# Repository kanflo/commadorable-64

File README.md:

# Commadorable 64

An adorable Commodore 64 desktop ornament. Blog post [here](http://johan.kanflo.com/the-commadorable-64/).

**Howto**

Assuming you have cloned the EOR git and set your wifi credentials:

```
export EOR_ROOT=/path/to/esp-open-rtos
cd $EOR_ROOT
git clone https://github.com/kanflo/eor-arduino-compat.git extras/arduino-compat
git clone https://github.com/kanflo/eor-adafruit-ili9341.git extras/ili9341
git clone https://github.com/kanflo/eor-cli.git extras/cli
cd /path/to/wherever
git clone https://github.com/kanflo/commadorable-64.git
cd commadorable-64
make -j8 && make flash
```

**Ordering the PCB**

The PCBs can be ordered from DirtyPCBs.com, [without touch](http://dirtypcbs.com/view.php?share=18116&accesskey=5cb9ea9c4754e5c9102b4350393b244e) or [with touch](http://dirtypcbs.com/view.php?share=18114&accesskey=f7144fbd88f9270b40ccc2829f08ee2f). If you use these links to order I will receive a $1 credit :)

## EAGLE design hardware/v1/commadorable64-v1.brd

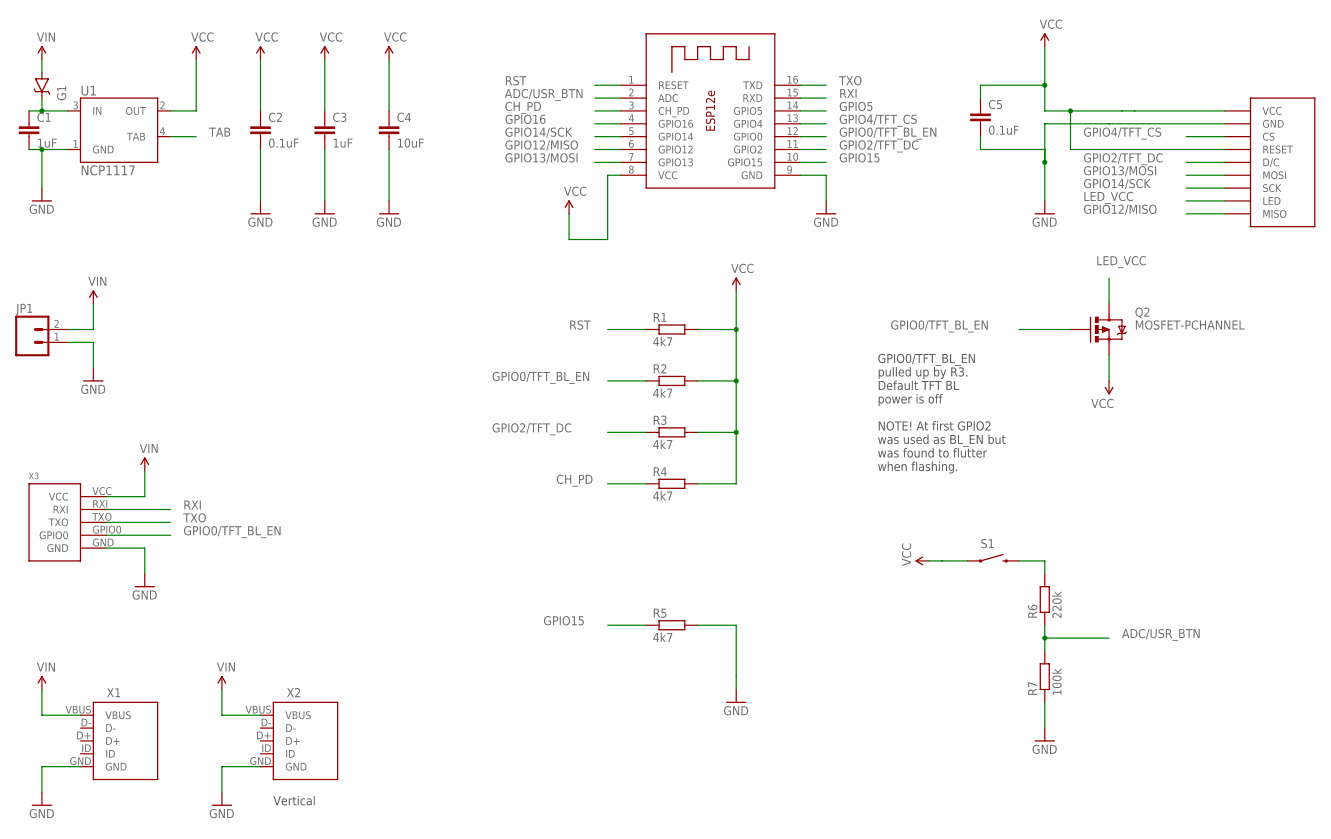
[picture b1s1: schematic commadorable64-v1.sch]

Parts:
C1, C3: 1uF; 0603-CAP
C2, C5: 0.1uF; 0603-CAP
C4: 10uF; 0603-CAP
G1: DIODE-SCHOTTKYSOD-123FL; SOD-123FL
J2: SPI_TFT_DISPLAY; SPI_DISPLAY
JP1: M02PTH; 1X02
Q2: MOSFET-PCHANNEL; SOT23-3
R1, R2, R3, R4, R5: 4k7; R0603
R6: 220k; R0603
R7: 100k; R0603
S1: SWITCH-MOMENTARY-2SMD-1101NE; TACTILE-SWITCH-1101NE
U1: NCP1117; SOT223
U2: ESP-12E
X1: MICRO_USB_TH
X2: MICRO_USB_TH_VERTICAL
X3: ESPROGESPROG-DEVICE; ESPROG

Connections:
ADC/USR_BTN: R6.1, R7.2, U2.2 (ADC)
CH_PD: R4.1, U2.3 (CH_PD)
GND: C1.2, C2.2, C3.2, C4.2, C5.2, J2.GND, JP1.1, R5.2, R7.1, U1.1 (GND), U2.9 (GND), X1.GND, X2.GND, X3.GND
GPIO0/TFT_BL_EN: Q2.1 (G), R2.1, U2.12 (GPIO0), X3.GPIO0
GPIO2/TFT_DC: J2.D/C, R3.1, U2.11 (GPIO2)
GPIO4/TFT_CS: J2.CS, U2.13 (GPIO4)
GPIO5: U2.14 (GPIO5)
GPIO12/MISO: J2.MISO, U2.6 (GPIO12)
GPIO13/MOSI: J2.MOSI, U2.7 (GPIO13)
GPIO14/SCK: J2.SCK, U2.5 (GPIO14)
GPIO15: R5.1, U2.10 (GPIO15)
GPIO16: U2.4 (GPIO16)
LED_VCC: J2.LED, Q2.3 (D)
unnamed: C1.1, G1.C, U1.3 (IN)
unnamed: R6.2, S1.2
RST: R1.1, U2.1 (RESET)
RXI: U2.15 (RXD), X3.RXI
TAB: U1.4 (TAB)
TXO: U2.16 (TXD), X3.TXO
VCC: C2.1, C3.1, C4.1, C5.1, J2.RESET, J2.VCC, Q2.2 (S), R1.2, R2.2, R3.2, R4.2, S1.1, U1.2 (OUT), U2.8 (VCC)
VIN: G1.A, JP1.2, X1.VBUS, X2.VBUS, X3.VCC

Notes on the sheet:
GPIO0/TFT_BL_EN pulled up by R3. Default TFT BL power is off NOTE! At first GPIO2 was used as BL_EN but was found to flutter when flashing.
Vertical

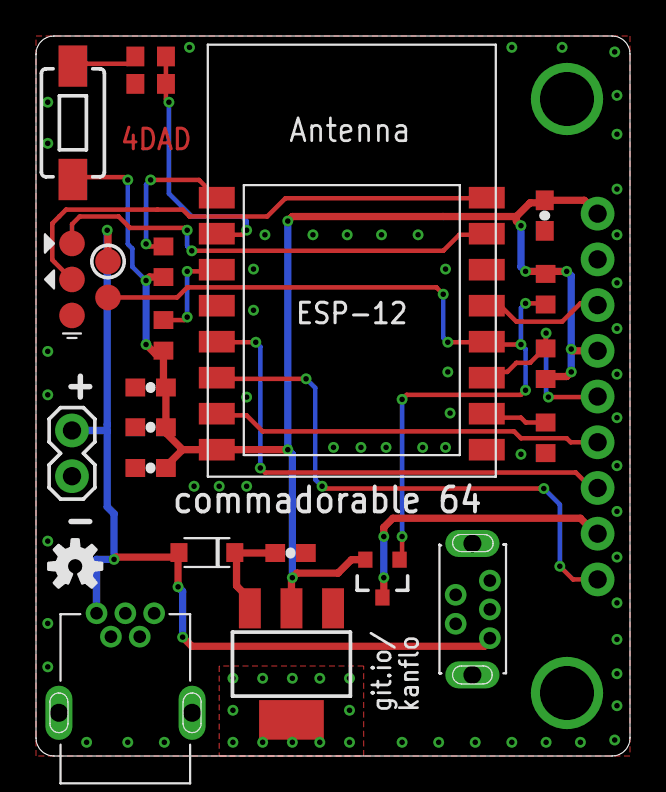
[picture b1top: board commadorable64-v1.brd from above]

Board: 2 copper layers, 33.0 x 40.0 mm, 23 parts (1 on the bottom side), 18 nets.

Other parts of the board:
U$1: OSHW-LOGO-S

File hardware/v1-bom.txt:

BOM for Commadoraboe 64 with and without touch

Part Value       Package           Description
------------------------------------------------------------------------------
C1   1uF         0603              Capacitor
C2   0.1uF       0603              Capacitor
C3   1uF         0603              Capacitor
C4   10uF        0603              Capacitor
C5   0.1uF       0603              Capacitor
G1               SOD-123FL         SCHOTTKY DIODE
J1               1x14              Standard 15-pin 0.1" header
JP1              1X02              Standard 2-pin 0.1" header
JP2, JP3         1X01              For mounting support on C64 touch variant
Q2               SOT23-3           MOSFET-PCHANNEL
R1   4k7         R0603             Resistor
R2   4k7         R0603             Resistor
R3   4k7         R0603             Resistor
R4   4k7         R0603             Resistor
R5   4k7         R0603             Resistor
R6   220k        R0603             Resistor
R7   100k        R0603             Resistor
S1               Tactile switch    3x6x2.5mm tactile switch from eBay
U1   3.3V        SOT223            NCP1117
U2               ESP-12E           ESP12e module
X1                                 Micro USB through hole connector from eBay
X2                                 Vertical micro USB through hole connector from eBay
X3                                 ESPROG (pads included on PCB, no mounting needed)

Please see http://johan.kanflo.com/the-commadorable-64/ for links to the
switch and USB connectors.

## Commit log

2016-08-15 Initial app commit
2016-08-15 Added schematics
2016-08-15 Added screenshot
2016-08-23 Added ESP8266 Arduino version of the Commadorable 64 demo
2016-08-28 Added BOM
2016-10-12 Added DirtyPCBs.com links for ordering
2016-12-18 Updated to latest version of EOR
2017-07-11 Renamed boards for TFT size clarity
2017-07-11 Added silkscreen, separated R6, R7
2017-07-11 Added silkscreen
2017-07-11 Added build sheets to aid PCB mounting
2017-07-11 Exclude build directory
2017-11-24 Update v1-bom.txt
    added and redo some descritption
2017-11-24 add comment to the XPT2046 Library
    add Link to the XPT2046 Lib cause it is not in the Arduino Library Manager

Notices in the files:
parts and their libraries:
SparkFun-Electromechanical: Licensing: Creative Commons ShareAlike 4.0 International - https://creativecommons.org/licenses/by-sa/4.0
